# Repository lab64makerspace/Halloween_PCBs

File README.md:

## Halloween_PCBs

This repository has files associated with the lab64 Halloween PCB design workshop and the lab64 Halloween PCB soldering workshop.

The first group of PCB outlines (pumpkin, ghost, and cat) are provided so that folks can try the process of importing a board outline into KiCAD. Additional graphic features may be easily added by placing additional .dxf format graphics files on the appropriate PCB layer. For example, to emphasize the eyes of the ghost one may wish to import the file ghost_eyes.dxf onto the F.Silk layer when the board is open in Pcbnew. The color of soldermask and silkscreen may be selected when the boards files are sent to the fabrication vendor.

You can open the .dxf files in graphics programs such as Inkscape to add features. Just add the features you want, save the file, delete the original objects and save the additional features as a new .dxf file. This is how ghost_eyes.dxf was generated. Then to add the features to the PCB, simply execute a second import step onto the appropriate layer and viola!

If there are questions or concerns please let me know via email to steven dot clark at stanford dot edu

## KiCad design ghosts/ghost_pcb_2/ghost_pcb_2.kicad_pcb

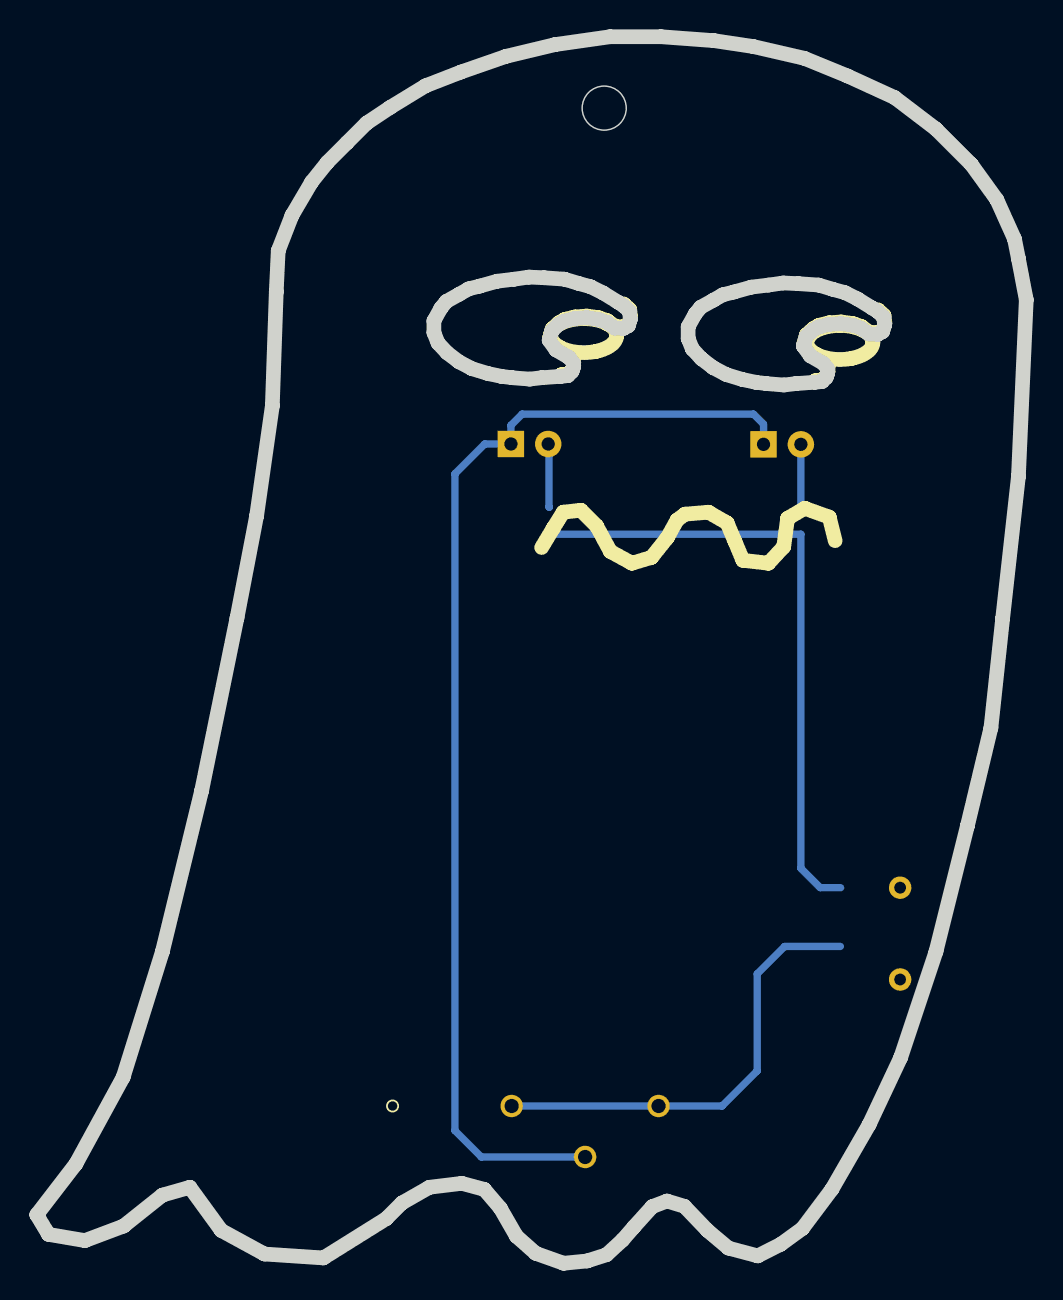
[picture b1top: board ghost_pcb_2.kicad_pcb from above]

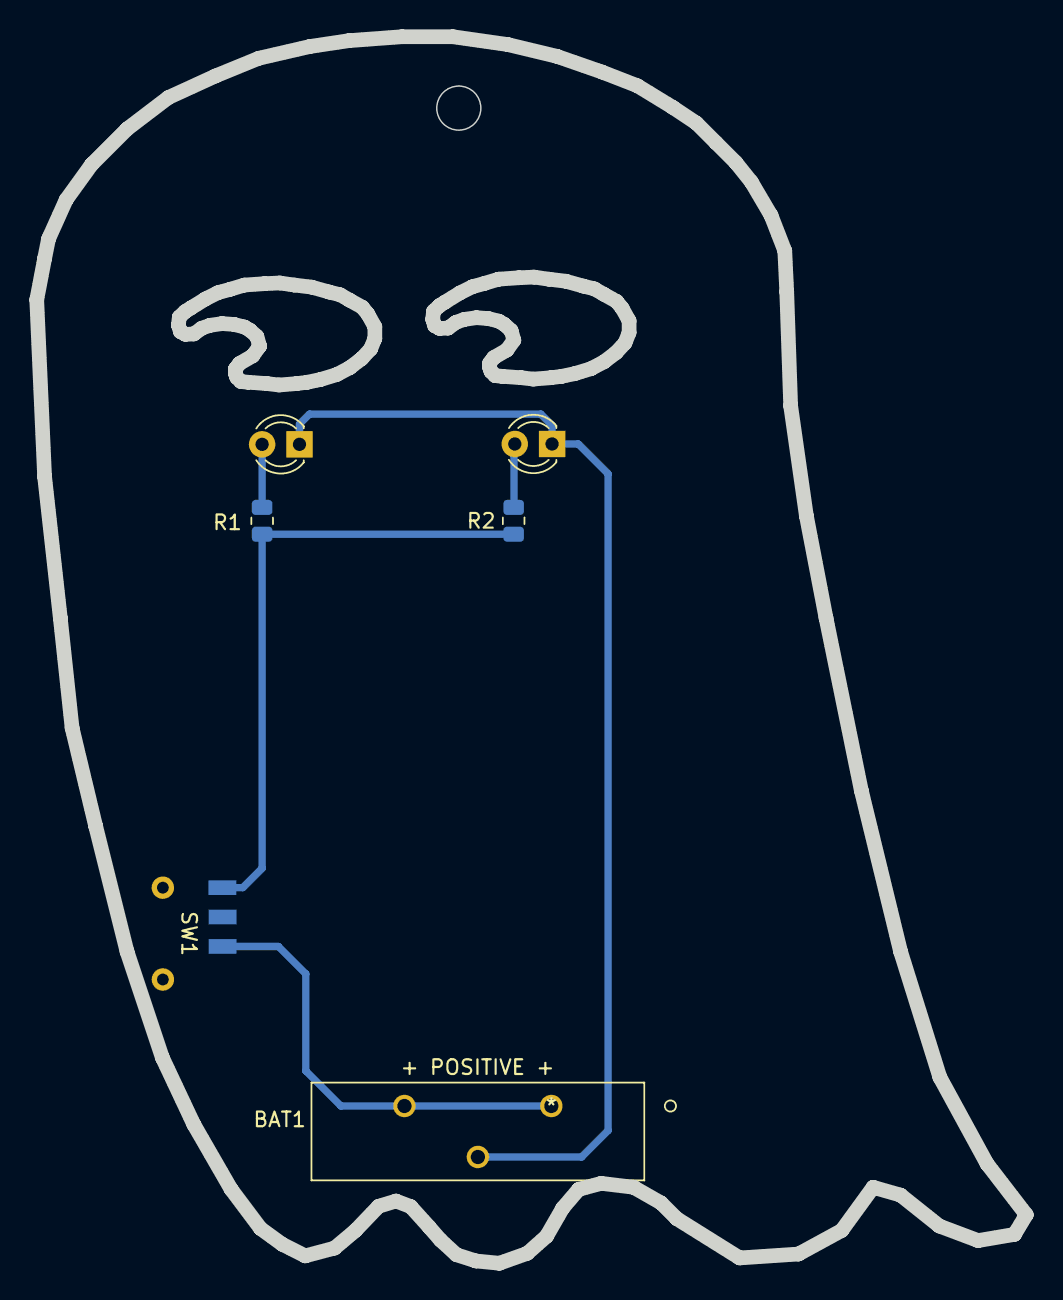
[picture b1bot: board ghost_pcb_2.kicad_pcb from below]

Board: 2 copper layers, 67.4 x 83.5 mm, 6 parts (6 on the bottom side), 5 nets.

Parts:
BAT1: BH-125A-1; BatteryHolder_AdamTech_BH-125A-1
D1, D2: LED per Chart; LED_D3.0mm
R1, R2: 47 Ohms; R_0805_2012Metric
SW1: SMT_SPDT; SMT_Mini_Slide_Switch

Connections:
+BATT: BAT1.POS1, BAT1.POS2, SW1.3
GND: BAT1.NEG, D1.1, D2.1
unnamed: D1.2, R1.2
unnamed: D2.2, R2.2
unnamed: R1.1, R2.1, SW1.1

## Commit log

2021-10-10 Initial README commit
2021-10-10 Halloween_PCBs
2021-10-10 Loading graphics
2021-10-12 Adding footprints
2021-10-12 Adding_Battery_Holder_Footprint
2021-10-12 Adding_SMT_slide_switch
2021-10-18 Updating footprints / schematics
2021-10-18 Updating all PCBS, etc.
2021-10-30 Bunch of changes

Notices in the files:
parts and their libraries:
Copyright 2021 Accelerated Designs. All rights reserved.
